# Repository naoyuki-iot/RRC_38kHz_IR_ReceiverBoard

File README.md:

# RRC_38kHz_IR_ReceiverBoard
- To use in controlling autonomous robots.

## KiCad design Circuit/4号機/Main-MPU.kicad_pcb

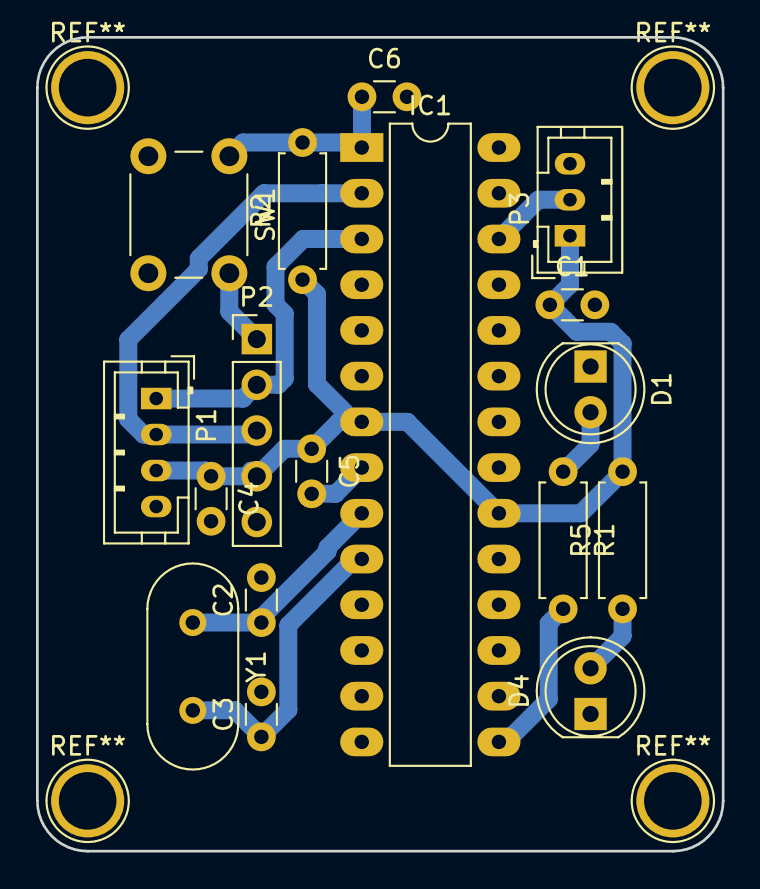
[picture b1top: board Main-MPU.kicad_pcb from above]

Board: 2 copper layers, 38.1 x 45.2 mm, 17 parts (0 on the bottom side), 11 nets.

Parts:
C1, C4, C5, C6: 1uF; C_Disc_D3.0mm_W1.6mm_P2.50mm
C2, C3: 22pF; C_Disc_D3.0mm_W1.6mm_P2.50mm
D1: Status; LED_D5.0mm
D4: Power; LED_D5.0mm
IC1: ATMEGA328P-P; DIP-28_W7.62mm_LongPads
P1: Serial; JST_PH_B4B-PH-K_04x2.00mm_Straight
P2: Write; Pin_Header_Straight_1x05_Pitch2.54mm
P3: 38kHz_IR_Receive; JST_PH_B3B-PH-K_03x2.00mm_Straight
R1, R2, R5: 1k; R_Axial_DIN0207_L6.3mm_D2.5mm_P7.62mm_Horizontal
SW1: SW_PUSH; SW_PUSH_6mm_h7.3mm
Y1: Crystal; Crystal_HC49-4H_Vertical

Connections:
+5V: C1.1, C4.1, C5.1, IC1.7, IC1.20, P1.3, P2.4, P3.1, R2.1, R5.2
/38kHz_IR: IC1.26, P3.2
/N_Rst: C6.1, IC1.1, P2.1, R2.2, SW1.1
/Rx: IC1.2, P1.2, P2.3
/Tx: IC1.3, P1.1, P2.2
/Xtal: C3.1, IC1.10, Y1.2
GND: C1.2, C2.2, C3.2, C4.2, C5.2, C6.2, D1.1, D4.1, IC1.8, IC1.22, P1.4, P2.5, P3.3, SW1.2
unnamed: C2.1, IC1.9, Y1.1
unnamed: D1.2, R1.1
unnamed: D4.2, R5.1
unnamed: IC1.15, R1.2

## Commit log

2020-06-12 Create fp-info-cache
2020-08-14 create
    hoge
